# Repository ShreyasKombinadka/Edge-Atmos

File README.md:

## **Edge Atmos**

A local weather station built with no HAL and all custom drivers and libraries built from bare-metal register level coding.

## Overview
- Built on STM32 board with no HAL.
- All the driver and libraries are custom built.

## Status
- [ ] Firmware
- [ ] Hardware 
- [ ] Completed

## Libraries built
1. I2C driver
2. LCD1602 driver
3. ASCII conversion library
4. AHT10 Temperature and humidity sensor driver
5. BMP280 Pressure sensor driver
6. GPIO driver
7. SPI driver
8. W25Q32 Flash memory driver
9. ST7789LCD TFT display driver
10. Font bitmap file

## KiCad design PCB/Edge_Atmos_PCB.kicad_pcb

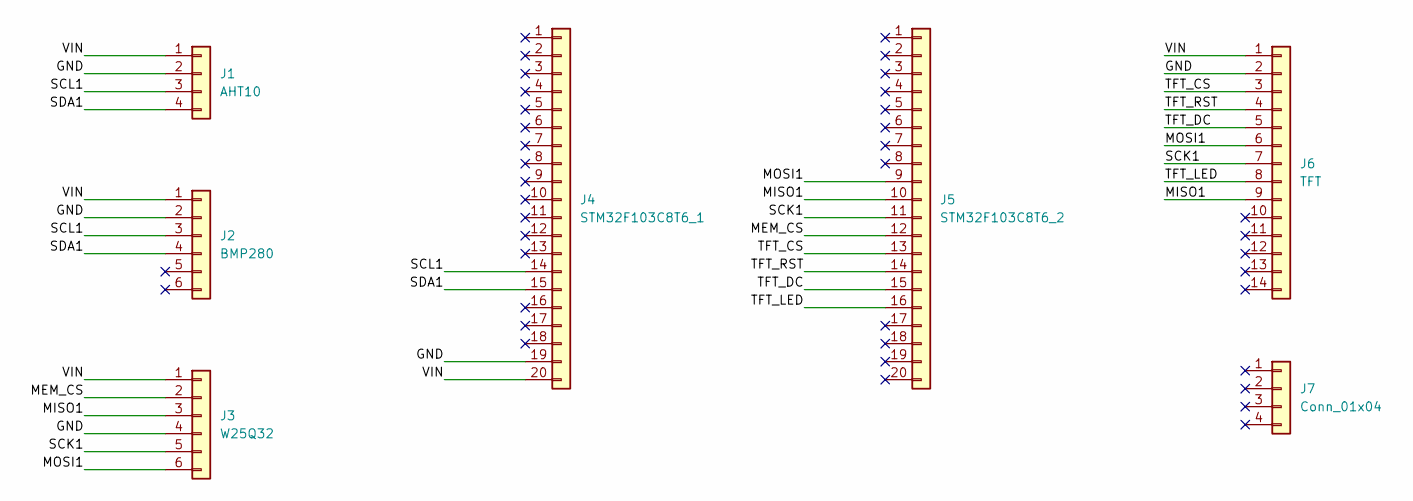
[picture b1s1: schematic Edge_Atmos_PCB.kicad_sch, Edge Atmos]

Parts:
J1: AHT10; PinSocket_1x04_P2.54mm_Vertical
J2: BMP280; PinSocket_1x06_P2.54mm_Vertical
J3: W25Q32; PinSocket_1x06_P2.54mm_Vertical
J4: STM32F103C8T6_1; PinSocket_1x20_P2.54mm_Vertical
J5: STM32F103C8T6_2; PinSocket_1x20_P2.54mm_Vertical
J6: TFT; PinSocket_1x14_P2.54mm_Vertical
J7: Conn_01x04; PinSocket_1x04_P2.54mm_Vertical

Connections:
/GND: J1.2, J2.2, J3.4, J4.19, J6.2
/MEM_CS: J3.2, J5.12
/MISO1: J3.3, J5.10, J6.9
/MOSI1: J3.6, J5.9, J6.6
/SCK1: J3.5, J5.11, J6.7
/SCL1: J1.3, J2.3, J4.14
/SDA1: J1.4, J2.4, J4.15
/TFT_CS: J5.13, J6.3
/TFT_DC: J5.15, J6.5
/TFT_LED: J5.16, J6.8
/TFT_RST: J5.14, J6.4
/VIN: J1.1, J2.1, J3.1, J4.20, J6.1

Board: 2 copper layers, 7 parts (2 on the bottom side), 12 nets, no tracks yet.

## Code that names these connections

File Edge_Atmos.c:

#include <stdint.h>

#include "I2C_MS/I2C1.h"
#include "SPI_MS/SPI1.h"
#include "AHT10_MS/AHT10.h"
#include "BMP280_MS/BMP280.h"
#include "W25Q32_MS/W25Q32.h"
#include "ASCII_MS/ASCII.h"
#include "ST7789LCD_MS/ST7789LCD.h"
#include "MS_COLOR/COLOR.h"

#define STM32F103xB
#include "STM32F103_CMSIS/stm32f1xx.h"

// Pins and Ports
#define MEM_CS 4         // Flash CS
#define MEM_CS_PORT 'A'  // Flash CS port
#define TFT_CS 3         // TFT display CS
#define TFT_CS_PORT 'A'  // TFT display CS port
#define TFT_DC 1         // TFT display DC
#define TFT_DC_PORT 'A'  // TFT display DC port
#define TFT_RST 2        // TFT display RST
#define TFT_RST_PORT 'A' // TFT display RST port
#define TFT_LED 0        // TFT display LED
#define TFT_LED_PORT 'A' // TFT display LED port
#define DISPLAY_ORIEN 1  // TFT display orientation/rotation

int main(void)
{
    i2c1_init();
    spi1_init(3, 0);

    st7789lcd_init(TFT_CS, TFT_CS_PORT, TFT_DC, TFT_DC_PORT, TFT_RST, TFT_RST_PORT, TFT_LED, TFT_LED_PORT, DISPLAY_ORIEN, 320, 240);
    st7789lcd_clear(MS_WHITE_16);
    st7789lcd_settext(16, 12);
    st7789lcd_addrst();
    st7789lcd_print("EDGE ATMOS", 10, 40, MS_BRIGHT_RED_16, 2);

    spi1_slaveset(MEM_CS, MEM_CS_PORT, 2);

    aht10_init();

    uint8_t FACTORY_CALIBRATION_DATA[24];
    bmp280_init(FACTORY_CALIBRATION_DATA);

    while (1)
    {
        float aht_temp = 0;
        float bmp_temp = 0;
        float humi = 0;
        float pres = 0;
        aht10_read(&aht_temp, &humi);
        bmp280_read(FACTORY_CALIBRATION_DATA, &pres, &bmp_temp);

        uint8_t aht_temp_char_arr[6];
        uint8_t bmp_temp_char_arr[6];
        uint8_t humi_char_arr[6];
        uint8_t pres_char_arr[6];
        num_float4digi_ascii(aht_temp, aht_temp_char_arr);
        num_float4digi_ascii(bmp_temp, bmp_temp_char_arr);
        num_float4digi_ascii(humi, humi_char_arr);
        num_float4digi_ascii(pres, pres_char_arr);

        st7789lcd_addrst();
        st7789lcd_print("TEMPERATURE :", 100, 10, MS_BLACK_16, 1);
        st7789lcd_colrst();
        st7789lcd_print(bmp_temp_char_arr, -16, 200, MS_YELLOW_16, 1);
        st7789lcd_print("'", -16, 5, MS_BLACK_16, 1);

        st7789lcd_colrst();
        st7789lcd_print("PRESURE :", 10, 10, MS_BLACK_16, 1);
        st7789lcd_colrst();
        st7789lcd_print(pres_char_arr, -16, 200, MS_GREEN_16, 1);
        st7789lcd_print("hpa", -16, 5, MS_BLACK_16, 1);

        st7789lcd_colrst();
        st7789lcd_print("HUMIDITY :", 10, 10, MS_BLACK_16, 1);
        st7789lcd_colrst();
        st7789lcd_print(humi_char_arr, -16, 200, MS_BLUE_16, 1);
        st7789lcd_print("%", -16, 5, MS_BLACK_16, 1);
    }
}

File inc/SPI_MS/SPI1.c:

#include "SPI1.h"
#include "./GPIO_MS/GPIO.h"
#include <stdint.h>

#define STM32F103xB
#include "stm32f1xx.h"

/* SPI1 Initialisation
CPHA & CPOL
Bit 0: Clock phase(CPHA).
Bit 1: Clock polarity(CPOL).
Allowed values:
0: FirstEdge: The first clock transition is the first data capture edge & IdleLow: CK to 0 when idle
1: SecondEdge: The second clock transition is the first data capture edge & IdleLow: CK to 0 when idle
2: FirstEdge: The first clock transition is the first data capture edge & IdleHigh: CK to 1 when idle
3: SecondEdge: The second clock transition is the first data capture edge & IdleHigh: CK to 1 when idle

BR
3 bits : Baud rate control.
Allowed values:
0: Div2: f_PCLK / 2
1: Div4: f_PCLK / 4
2: Div8: f_PCLK / 8
3: Div16: f_PCLK / 16
4: Div32: f_PCLK / 32
5: Div64: f_PCLK / 64
6: Div128: f_PCLK / 128
7: Div256: f_PCLK / 256
*/
void spi1_init(uint8_t CPOL_CPHA, uint8_t BR) // SPI1 Initialisation00
{
    RCC->APB2ENR |= (1 << 12); // Enable SPI1
    gpio_en('A');              // Enable GPIOA PORT

    gpio_setup(5, 'A', 3, 2); // SCK1 (50MHz alternate push pull)
    gpio_setup(6, 'A', 0, 1); // MISO1 (Floating input)
    gpio_setup(7, 'A', 3, 2); // MOSI1 (50MHz alternate push pull)

    SPI1->CR1 |= (1 << 2);           // Master mode
    SPI1->CR1 |= (3 << 8);           // Ignore NSS and assume HIGH internally
    SPI1->CR1 &= ~3;                 // CLK and Data read write bits clear
    SPI1->CR1 |= (CPOL_CPHA & 0x03); // CLK and Data read write configuration
    SPI1->CR1 &= ~(7 << 3);          // CLK devider select bits clear
    SPI1->CR1 |= ((BR & 0x07) << 3); // CLK devider select for SPI CLK
    SPI1->CR1 &= ~(1 << 11);         // 8bit mode
    SPI1->CR1 |= (1 << 6);           // SPI enabled
}

void spi1_slaveset(uint8_t SLAVE_CS, uint8_t SLAVE_CS_PIN_PORT, uint8_t MODE) // Add slave select pin
{
    gpio_en(SLAVE_CS_PIN_PORT); // Enable GPIO PORT

    gpio_setup(SLAVE_CS, SLAVE_CS_PIN_PORT, MODE, 0); // Setup push pull mode

    spi1_slaveselect(SLAVE_CS, SLAVE_CS_PIN_PORT, 0); // De-select slave device by default
}

void spi1_slaveselect(uint8_t SLAVE_CS, uint8_t SLAVE_CS_PIN_PORT, uint8_t SELECT) // Slave selection
{
    if (SELECT)
        gpio_setreset(SLAVE_CS, SLAVE_CS_PIN_PORT, 0); // Pull the slave line low
    else
        gpio_setreset(SLAVE_CS, SLAVE_CS_PIN_PORT, 1); // Pull the slave line high
}

void spi1_8wf1byte(uint8_t DATA_W) // SPI fast write 1byte
{
    while (!(SPI1->SR & (1 << 1))) // Wait till the Tx buffer is empty
        ;
    SPI1->DR = DATA_W; // Load data to DR to transmit
}

void spi1_8w1byte(uint8_t DATA_W) // SPI write 1byte
{
    (void)SPI1->SR; // Clear flags
    (void)SPI1->DR; // Clear DR

    while (!(SPI1->SR & (1 << 1))) // Wait till the Tx buffer is empty
        ;
    SPI1->DR = DATA_W; // Load data to DR to transmit

    while (!(SPI1->SR & 1)) // Wait till the Rx buffer is not empty
        ;
    (void)SPI1->DR; // Clear DR

    while (SPI1->SR & (1 << 7)) // Wait till SPI is completed and DR is free
        ;
}

uint8_t spi1_8r1byte() // SPI read 1byte
{
    (void)SPI1->SR; // Clear flags
    (void)SPI1->DR; // Clear DR

    while (!(SPI1->SR & (1 << 1))) // Wait till the Tx buffer is empty
        ;
    SPI1->DR = 0; // Send a dummy byte

    while (!(SPI1->SR & 1)) // Wait till the Rx buffer is not empty
        ;
    uint8_t temp = SPI1->DR; // Load the received data from DR

    while (SPI1->SR & (1 << 7)) // Wait till SPI is completed and DR is free
        ;

    return temp; // Return the recived data
}

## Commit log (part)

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2026-04-04 Code to read from temp sensor using I2C communication
2026-04-04 Added .gitignore and README files
2026-04-12 Trying building custom libraries
2026-04-12 Implimented a custom i2c library and used it
2026-06-13 Testing lcd lib
2026-06-13 I2C and LCD libraries are functional on hardware
2026-06-14 The LCD display is working corrcetly
2026-06-14 Updated LCD library with char fuction
2026-06-14 Working on ATH10 lib
2026-06-15 Working on AHT10 lib
2026-06-17 Working on AHT10 sensor integration
2026-06-17 Completed AHT10 sensor intigration
2026-06-18 Fixed some unwanted delays
2026-06-18 Building a BMP280 library
2026-06-18 Working on BMP280 intigration
2026-06-18 Working on BMP280 intigration and solving ascii lib problems
2026-06-19 Working on the ascii library
2026-06-20 Working on display functions and sensor intigration
2026-06-21 Solved out of bounds wright for pressure values charrecter buffer
2026-06-21 BMP280 sensor intigration is done
2026-06-22 Completed sensor intigration
2026-06-23 Building SPI library
2026-06-24 Updated SPI lib
2026-06-24 Updating libraries
2026-06-24 Working on the SPI and flash memory library
2026-06-26 Working on flash memeory integrtion
2026-06-27 Updating W25Q32 lib
2026-06-27 Updating W25Q32 and SPI1 lib
2026-06-29 Flash JEDEC ID test to varify its functionality
2026-06-29 Flash read & write test
2026-06-29 Completed flash memory intigration
2026-06-30 Starting on Graphics library for TFT 2.8 LCD display
2026-06-30 Writing a GPIO driver
2026-06-30 Updating drivers with intigration of GPIO driver and removing unwanted functions
